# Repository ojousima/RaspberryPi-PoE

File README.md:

#Nothing to see here, move along.

This repository remains only for historical purposes, the official repository has been moved to https://github.com/Ell-i/ELL-i-KiCAD-Boards.

# RaspberryPi-PoE
PoE shield for Raspberry Pi+ and 2. Made in KiCAD

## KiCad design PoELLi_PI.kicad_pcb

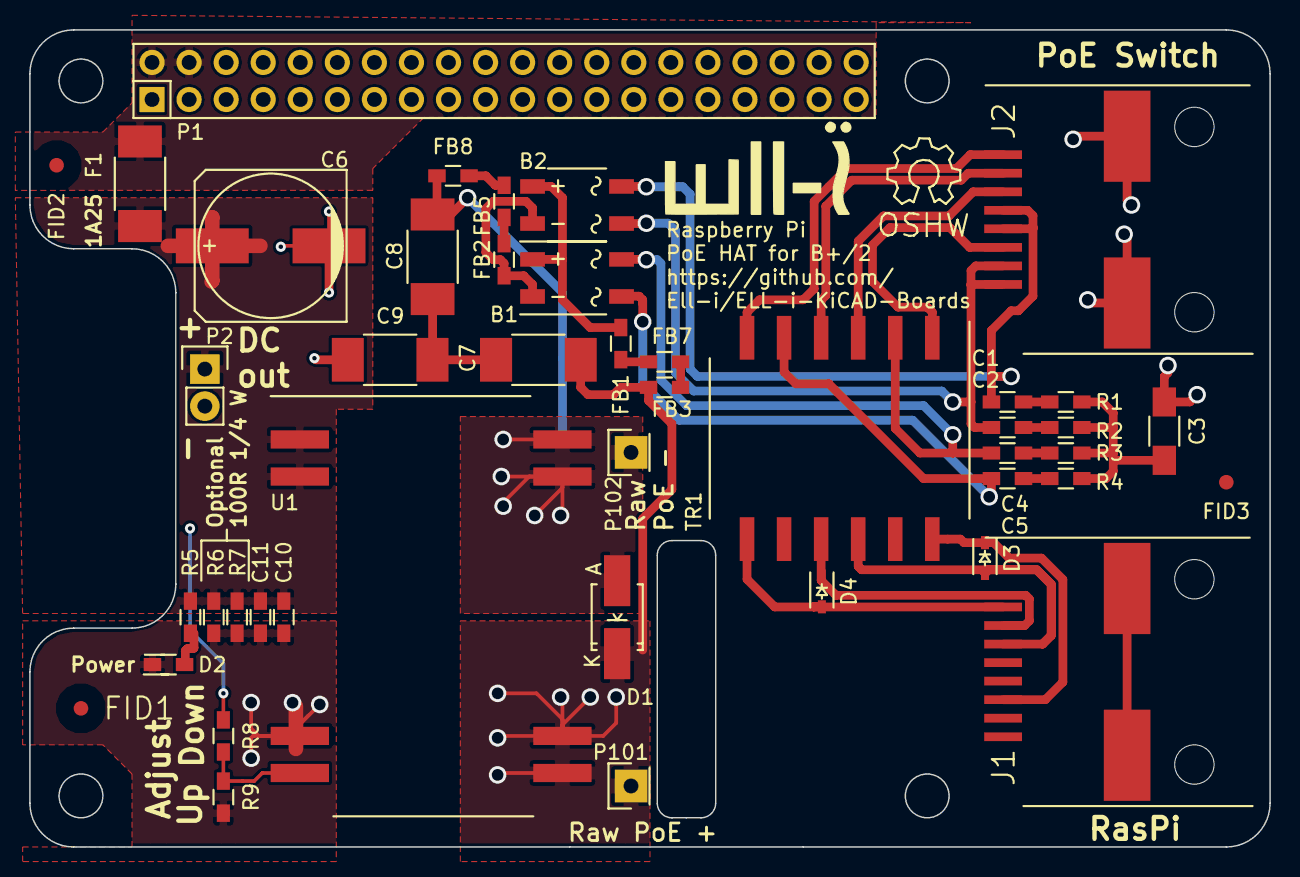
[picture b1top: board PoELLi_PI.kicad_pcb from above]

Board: 2 copper layers, 85.0 x 56.0 mm, 46 parts (0 on the bottom side), 32 nets.

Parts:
B1, B2: MB110S; TO-269AA
C1, C2, C4, C5: 10n 100V; R_0603_HandSoldering
C3: 1n 2kV; C_1206_HandSoldering
C6: 470u; c_elec_10x10
C7, C8, C9: 4n7 2kV; C_1812_HandSoldering
C10: 10n; R_0603_HandSoldering
C11: 10u; R_0603_HandSoldering
D1: SMA58; Diode-SMA_Handsoldering
D2: LED; R_0603_HandSoldering
D3, D4: TVS; SOD-323
F1: FUSE; C_1812_HandSoldering
FB1, FB2, FB3, FB5, FB7, FB8: FILTER; R_0603_HandSoldering
FID1, FID2, FID3: 1, 2 mm; Fiducial_2mm_dia
J1: RJSSE-5080; RJSSE-5380
J2: RJSSE-5380
LOGO101: OPEN_HARDWARE_1; Symbol_OSHW-Logo_SilkScreen
LOGO102: ELL-i; ELL-i_large
P1: CONN_02X20; Pin_Header_Straight_2x20
P2: CONN_01X02; Pin_Header_Straight_1x02
P101, P102: CONN_01X01; Pin_Header_Straight_1x01
R1, R2, R3, R4: 75R; R_0603_HandSoldering
R5: 180R; R_0603_HandSoldering
R6, R7: 100R 250 mW; R_0603_HandSoldering
R8, R9: R; R_0603_HandSoldering
TR1: 749012011; WE_749012011
U1: AG9800

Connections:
+5V: F1.2, P1.2, P1.4
/ADJ: R8.2, R9.1, U1.4
/AG_IN_+: C7.1, D1.2, FB7.2, P101.1, U1.5, U1.6
/AG_IN_-: C8.1, D1.1, FB8.2, P102.1, U1.7, U1.8
/AG_OUT_+: C6.1, C10.1, C11.1, F1.1, P2.1, R5.1, R6.1, R7.1, U1.1, U1.2
/POE_A+: B1.2, C5.1, TR1.5
/POE_A-: B1.4, C4.1, TR1.2
/POE_B+: B2.2, C2.1, J2.7, J2.8
/POE_B-: B2.4, C1.1, J2.4, J2.5
/RD+: D3.2, J1.3, TR1.10
/RD-: D3.1, J1.6, TR1.12
/RX+: J2.3, TR1.3
/RX-: J2.6, TR1.1
/TD+: D4.2, J1.1, TR1.7
/TD-: D4.1, J1.2, TR1.9
/TX+: J2.1, TR1.6
/TX-: J2.2, TR1.4
/VIN: B1.3, B2.3, FB1.1
GND: C6.2, C9.1, C10.2, C11.2, D2.2, P1.6, P1.9, P1.14, P1.20, P1.25, P1.30, P1.34, P1.39, P2.2, R6.2, R7.2, R9.2, U1.3
GNDA: C3.2, J2.9
GNDD: B1.1, B2.1, FB2.1
unnamed: C1.2, R1.1
unnamed: C2.2, R2.1
unnamed: C3.1, R1.2, R2.2, R3.2, R4.2
unnamed: C4.2, R3.1
unnamed: C5.2, R4.1
unnamed: C7.2, C8.2, C9.2
unnamed: D2.1, R5.2
unnamed: FB1.2, FB3.1
unnamed: FB2.2, FB5.1
unnamed: FB3.2, FB7.1
unnamed: FB5.2, FB8.1

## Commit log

2015-02-10 Add input protection diode
2015-02-10 unchecked schema, beginning PCB
2015-02-10 Add svg captures
2015-02-23 Add filtering to schematic
2015-02-27 First functional version before cosmetic changes
2015-02-27 Fix image printouts
2015-03-18 First production version, with ethernet connector holes fixed
2015-04-13 Version 1.0
2015-04-16 add printouts
2015-05-18 cosmetic fixes
2015-05-18 Add printout of schematic
2015-06-02 Add protection diodes, output connector, footprints for adjustment resistors
2015-06-22 Fix name on silkscreen, change fuse
2015-06-22 Add notice of moving repo
